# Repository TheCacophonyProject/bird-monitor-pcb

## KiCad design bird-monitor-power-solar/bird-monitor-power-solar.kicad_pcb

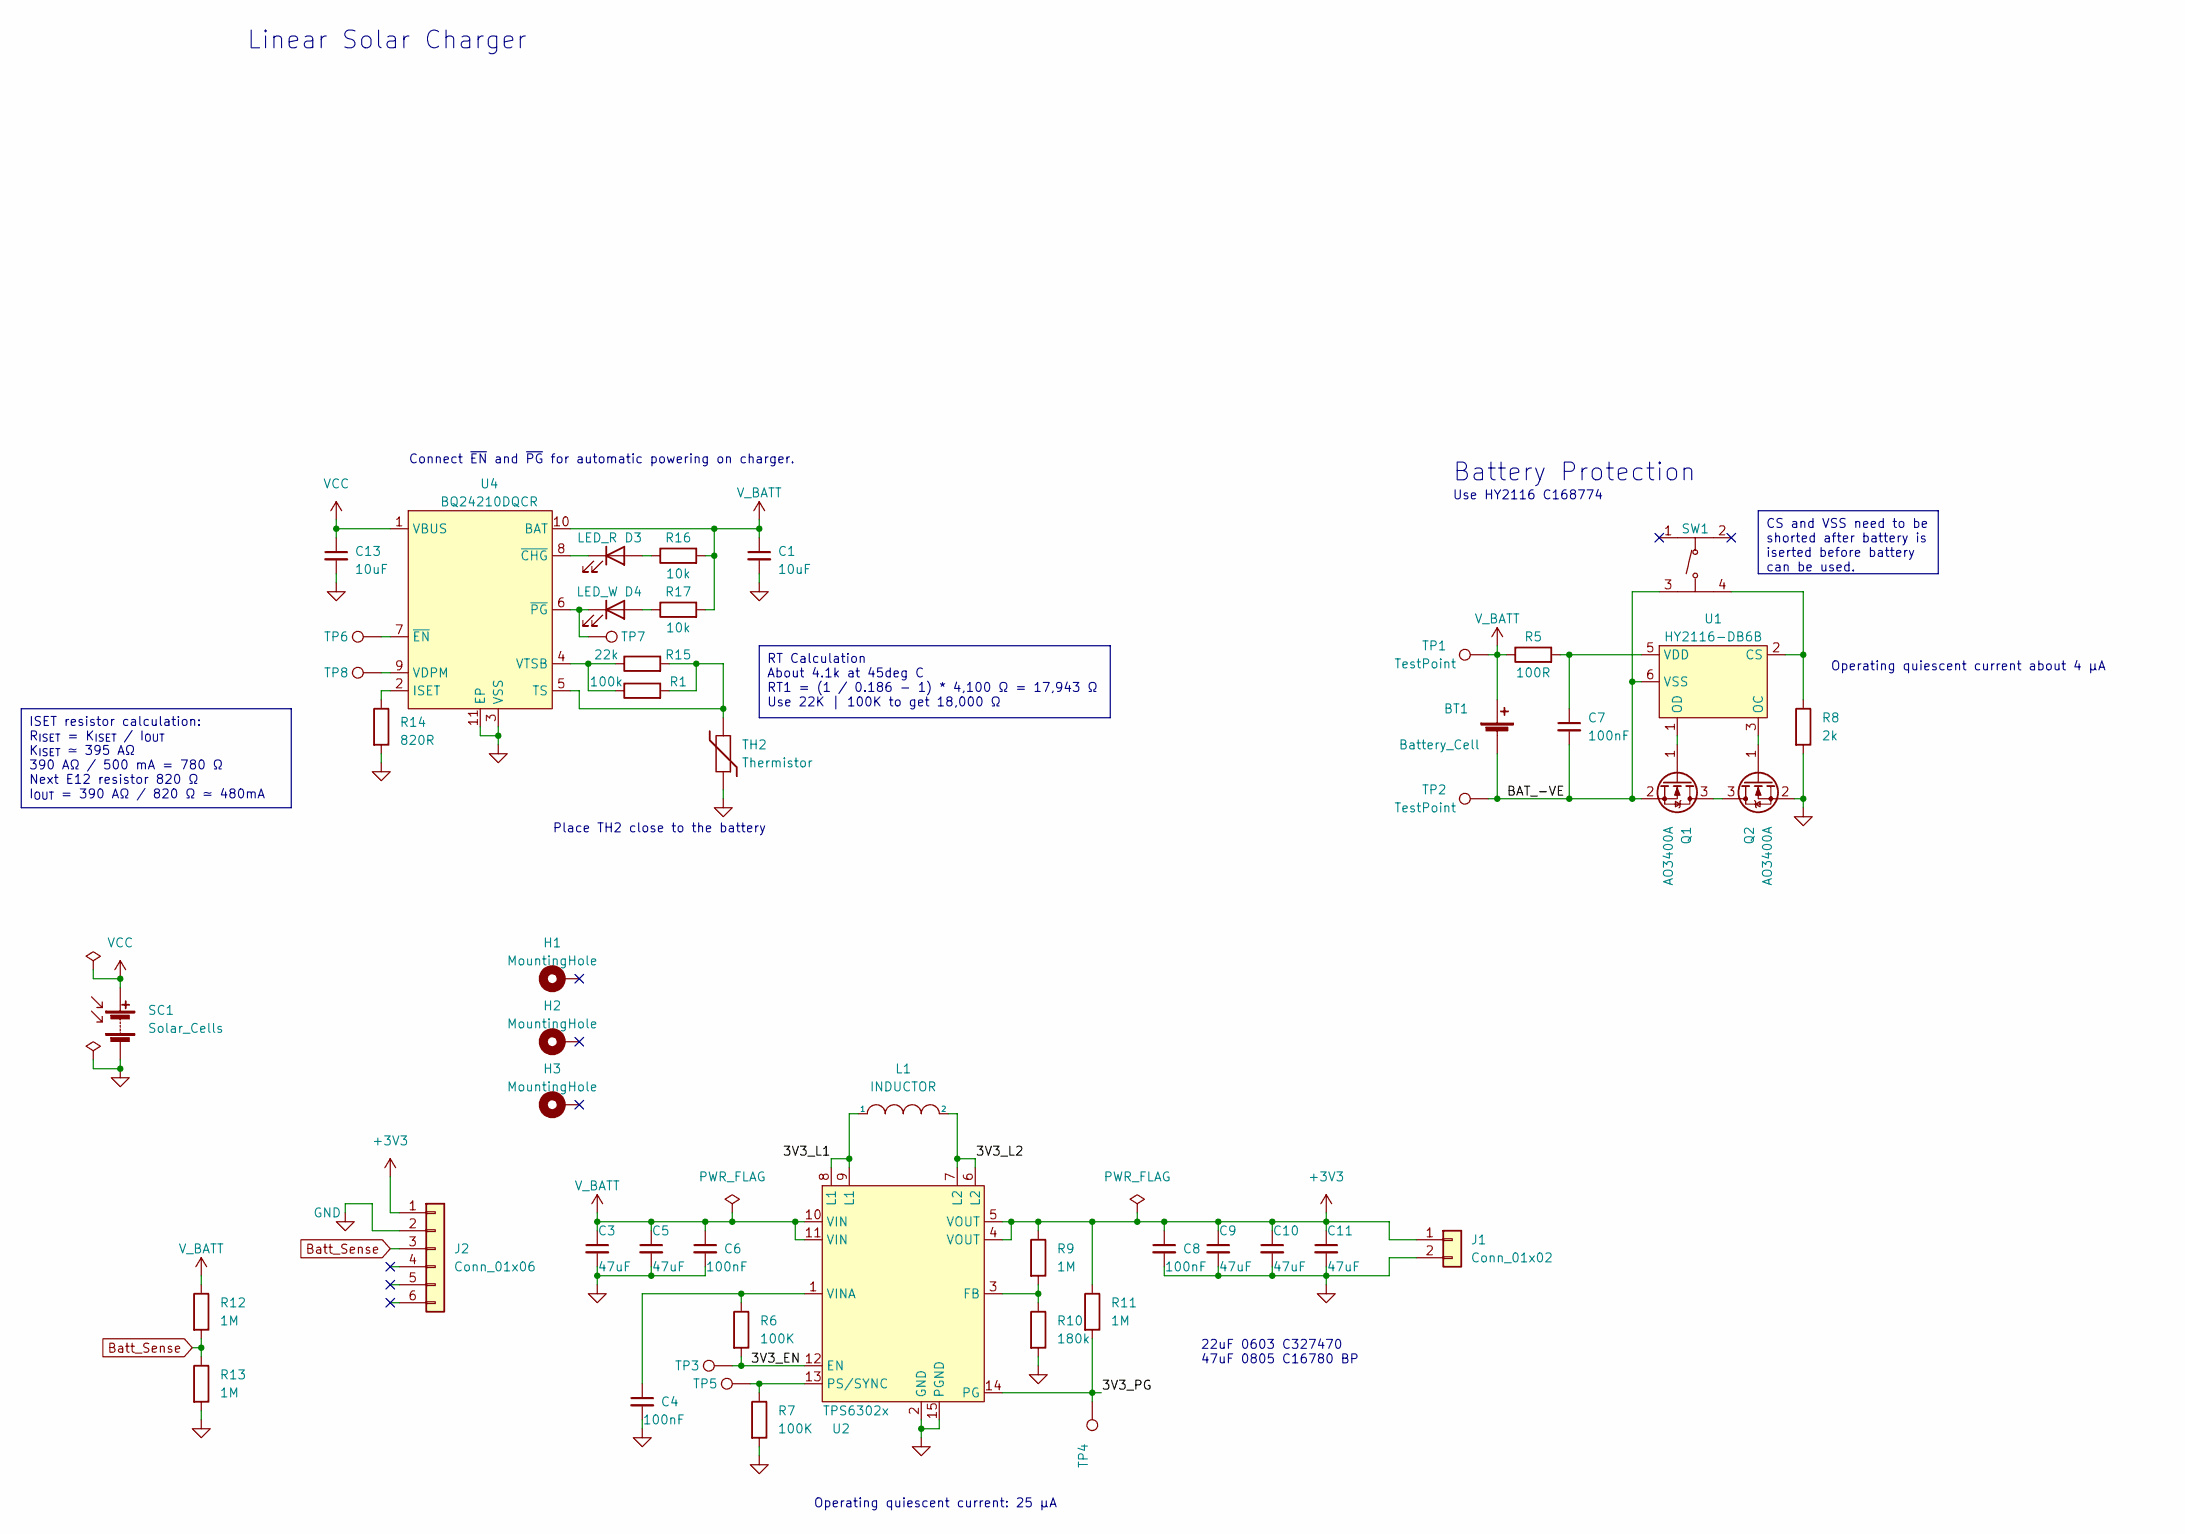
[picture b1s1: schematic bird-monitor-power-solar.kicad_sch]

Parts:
BT1: Battery_Cell; 18650_holder; LCSC C5290176
C1, C13: 10uF; C_0603_1608Metric; LCSC C96446
C3, C5, C9, C10, C11: 47uF; C_0805_2012Metric; LCSC C16780
C4, C6, C7, C8: 100nF; C_0402_1005Metric; LCSC C307331
D3: LED_R; LED_0603_1608Metric; LCSC C2286
D4: LED_W; LED_0603_1608Metric; LCSC C2290
H1, H2, H3: MountingHole; MountingHole_3.2mm_M3_DIN965_Pad
J1: Conn_01x02; PinHeader_1x02_P2.54mm_Vertical
J2: Conn_01x06; PinHeader_1x06_P2.54mm_Vertical
L1: INDUCTOR; IND-SMD_L6.6-W6.6_MCW-06XX; LCSC C169313
Q1, Q2: AO3400A; SOT-23; LCSC C20917
R1: 100k; R_0402_1005Metric; LCSC C25741
R5: 100R; R_0402_1005Metric; LCSC C25076
R6, R7: 100K; R_0402_1005Metric; LCSC C25741
R8: 2k; R_0603_1608Metric; LCSC C22975
R9, R11: 1M; R_0402_1005Metric; LCSC C26083
R10: 180k; R_0402_1005Metric; LCSC C409856
R12, R13: 1M; R_0603_1608Metric; LCSC C22935
R14: 820R; R_0603_1608Metric; LCSC C23253
R15: 22k; R_0402_1005Metric; LCSC C25768
R16, R17: 10k; R_0402_1005Metric; LCSC C25744
SC1: Solar_Cells; PinHeader_1x02_P2.54mm_Vertical
SW1: TS-1187A-B-A-B; SW-SMD_4P-L5.1-W5.1-P3.70-LS6.5-TL-2; LCSC Part C318884
TH2: Thermistor; R_0805_2012Metric; LCSC C95968
TP1, TP2, TP3, TP4, TP5, TP6, TP7, TP8: TestPoint; TestPoint_THTPad_D2.0mm_Drill1.0mm
U1: HY2116-DB6B; SOT-23-6; LCSC C168774
U2: TPS6302x; VSON-14_L4.0-W3.0-P0.50-BL-EP_TI_DSJ; LCSC C15483
U4: BQ24210DQCR; WSON-10-1EP_2x3mm_P0.5mm_EP0.84x2.4mm; LCSC Part C524795

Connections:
+3V3: C8.1, C9.1, C10.1, C11.1, J1.1, J2.1, R9.1, R11.1, U2.4 (VOUT), U2.5 (VOUT)
/3V3_EN: R6.2, TP3.1, U2.12 (EN)
/3V3_L1: L1.1, U2.8 (L1), U2.9 (L1)
/3V3_L2: L1.2, U2.6 (L2), U2.7 (L2)
/3V3_PG: R11.2, TP4.1, U2.14 (PG)
/BAT_-VE: BT1.2 (-), C7.2, Q1.2 (S), SW1.3, TP2.1, U1.6 (VSS)
Batt_Sense: J2.3, R12.2, R13.1
GND: C1.2, C3.2, C4.2, C5.2, C6.2, C8.2, C9.2, C10.2, C11.2, C13.2, J1.2, J2.2, Q2.2 (S), R7.2, R8.2, R10.2, R13.2, R14.2, SC1.2 (-), TH2.1, U2.2 (GND), U2.15 (PGND), U4.3 (VSS), U4.11 (EP)
unnamed: D3.2 (A), R16.1
unnamed: D3.1 (K), U4.8 (~CHG)
unnamed: D4.2 (A), R17.1
unnamed: D4.1 (K), TP7.1, U4.6 (~PG)
unnamed: Q1.3 (D), Q2.3 (D)
unnamed: Q1.1 (G), U1.1 (OD)
unnamed: Q2.1 (G), U1.3 (OC)
unnamed: R8.1, SW1.4, U1.2 (CS)
unnamed: C7.1, R5.2, U1.5 (VDD)
unnamed: R9.2, R10.1, U2.3 (FB)
unnamed: R7.1, TP5.1, U2.13 (PS/SYNC)
unnamed: C4.1, R6.1, U2.1 (VINA)
unnamed: R14.1, U4.2 (ISET)
unnamed: R1.2, R15.2, TH2.2, U4.5 (TS)
unnamed: TP8.1, U4.9 (VDPM)
unnamed: R1.1, R15.1, U4.4 (VTSB)
unnamed: TP6.1, U4.7 (~EN)
VCC: C13.1, SC1.1 (+), U4.1 (VBUS)
V_BATT: BT1.1 (+), C1.1, C3.1, C5.1, C6.1, R5.1, R12.1, R16.2, R17.2, TP1.1, U2.10 (VIN), U2.11 (VIN), U4.10 (BAT)

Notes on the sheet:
RT Calculation About 4.1k at 45deg C RT1 = (1 / 0.186 - 1) * 4,100 Ω = 17,943 Ω Use 22K | 100K to get 18,000 Ω
CS and VSS need to be shorted after battery is iserted before battery can be used.
ISET resistor calculation: R_{ISET} = K_{ISET} / I_{OUT} K_{ISET} ≃ 395 AΩ 390 AΩ / 500 mA = 780 Ω Next E12 resistor 820 Ω I_{OUT} = 390 AΩ / 820 Ω ≃ 480mA
Operating quiescent current about 4 μA
Battery Protection
Connect ~{EN} and ~{PG} for automatic powering on charger.
Use HY2116 C168774
Operating quiescent current: 25 μA
Place TH2 close to the battery
Linear Solar Charger
22uF 0603 C327470 47uF 0805 C16780 BP

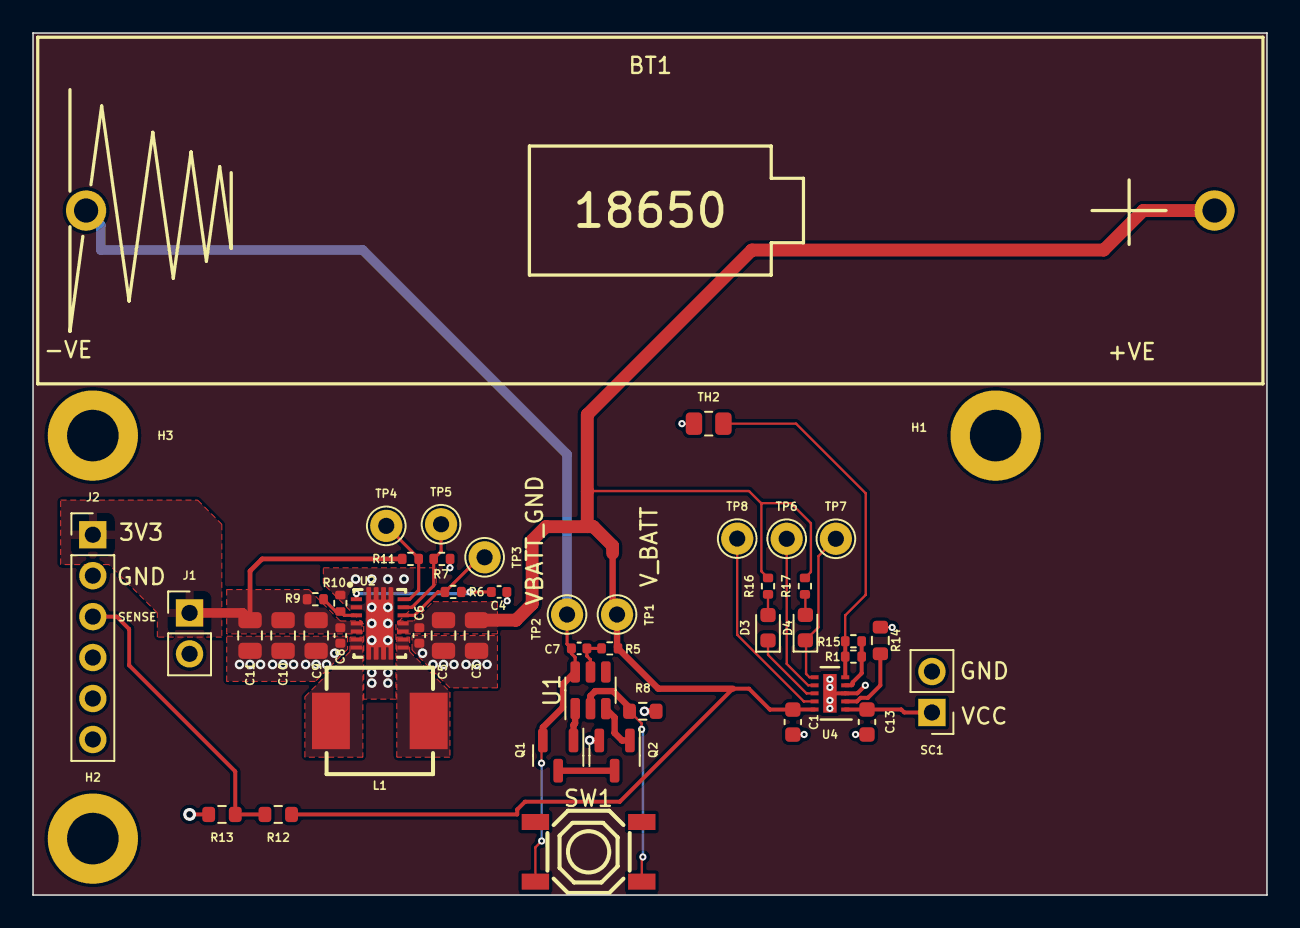
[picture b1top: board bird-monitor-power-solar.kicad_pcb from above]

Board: 4 copper layers, 76.5 x 53.5 mm, 50 parts (0 on the bottom side), 27 nets.

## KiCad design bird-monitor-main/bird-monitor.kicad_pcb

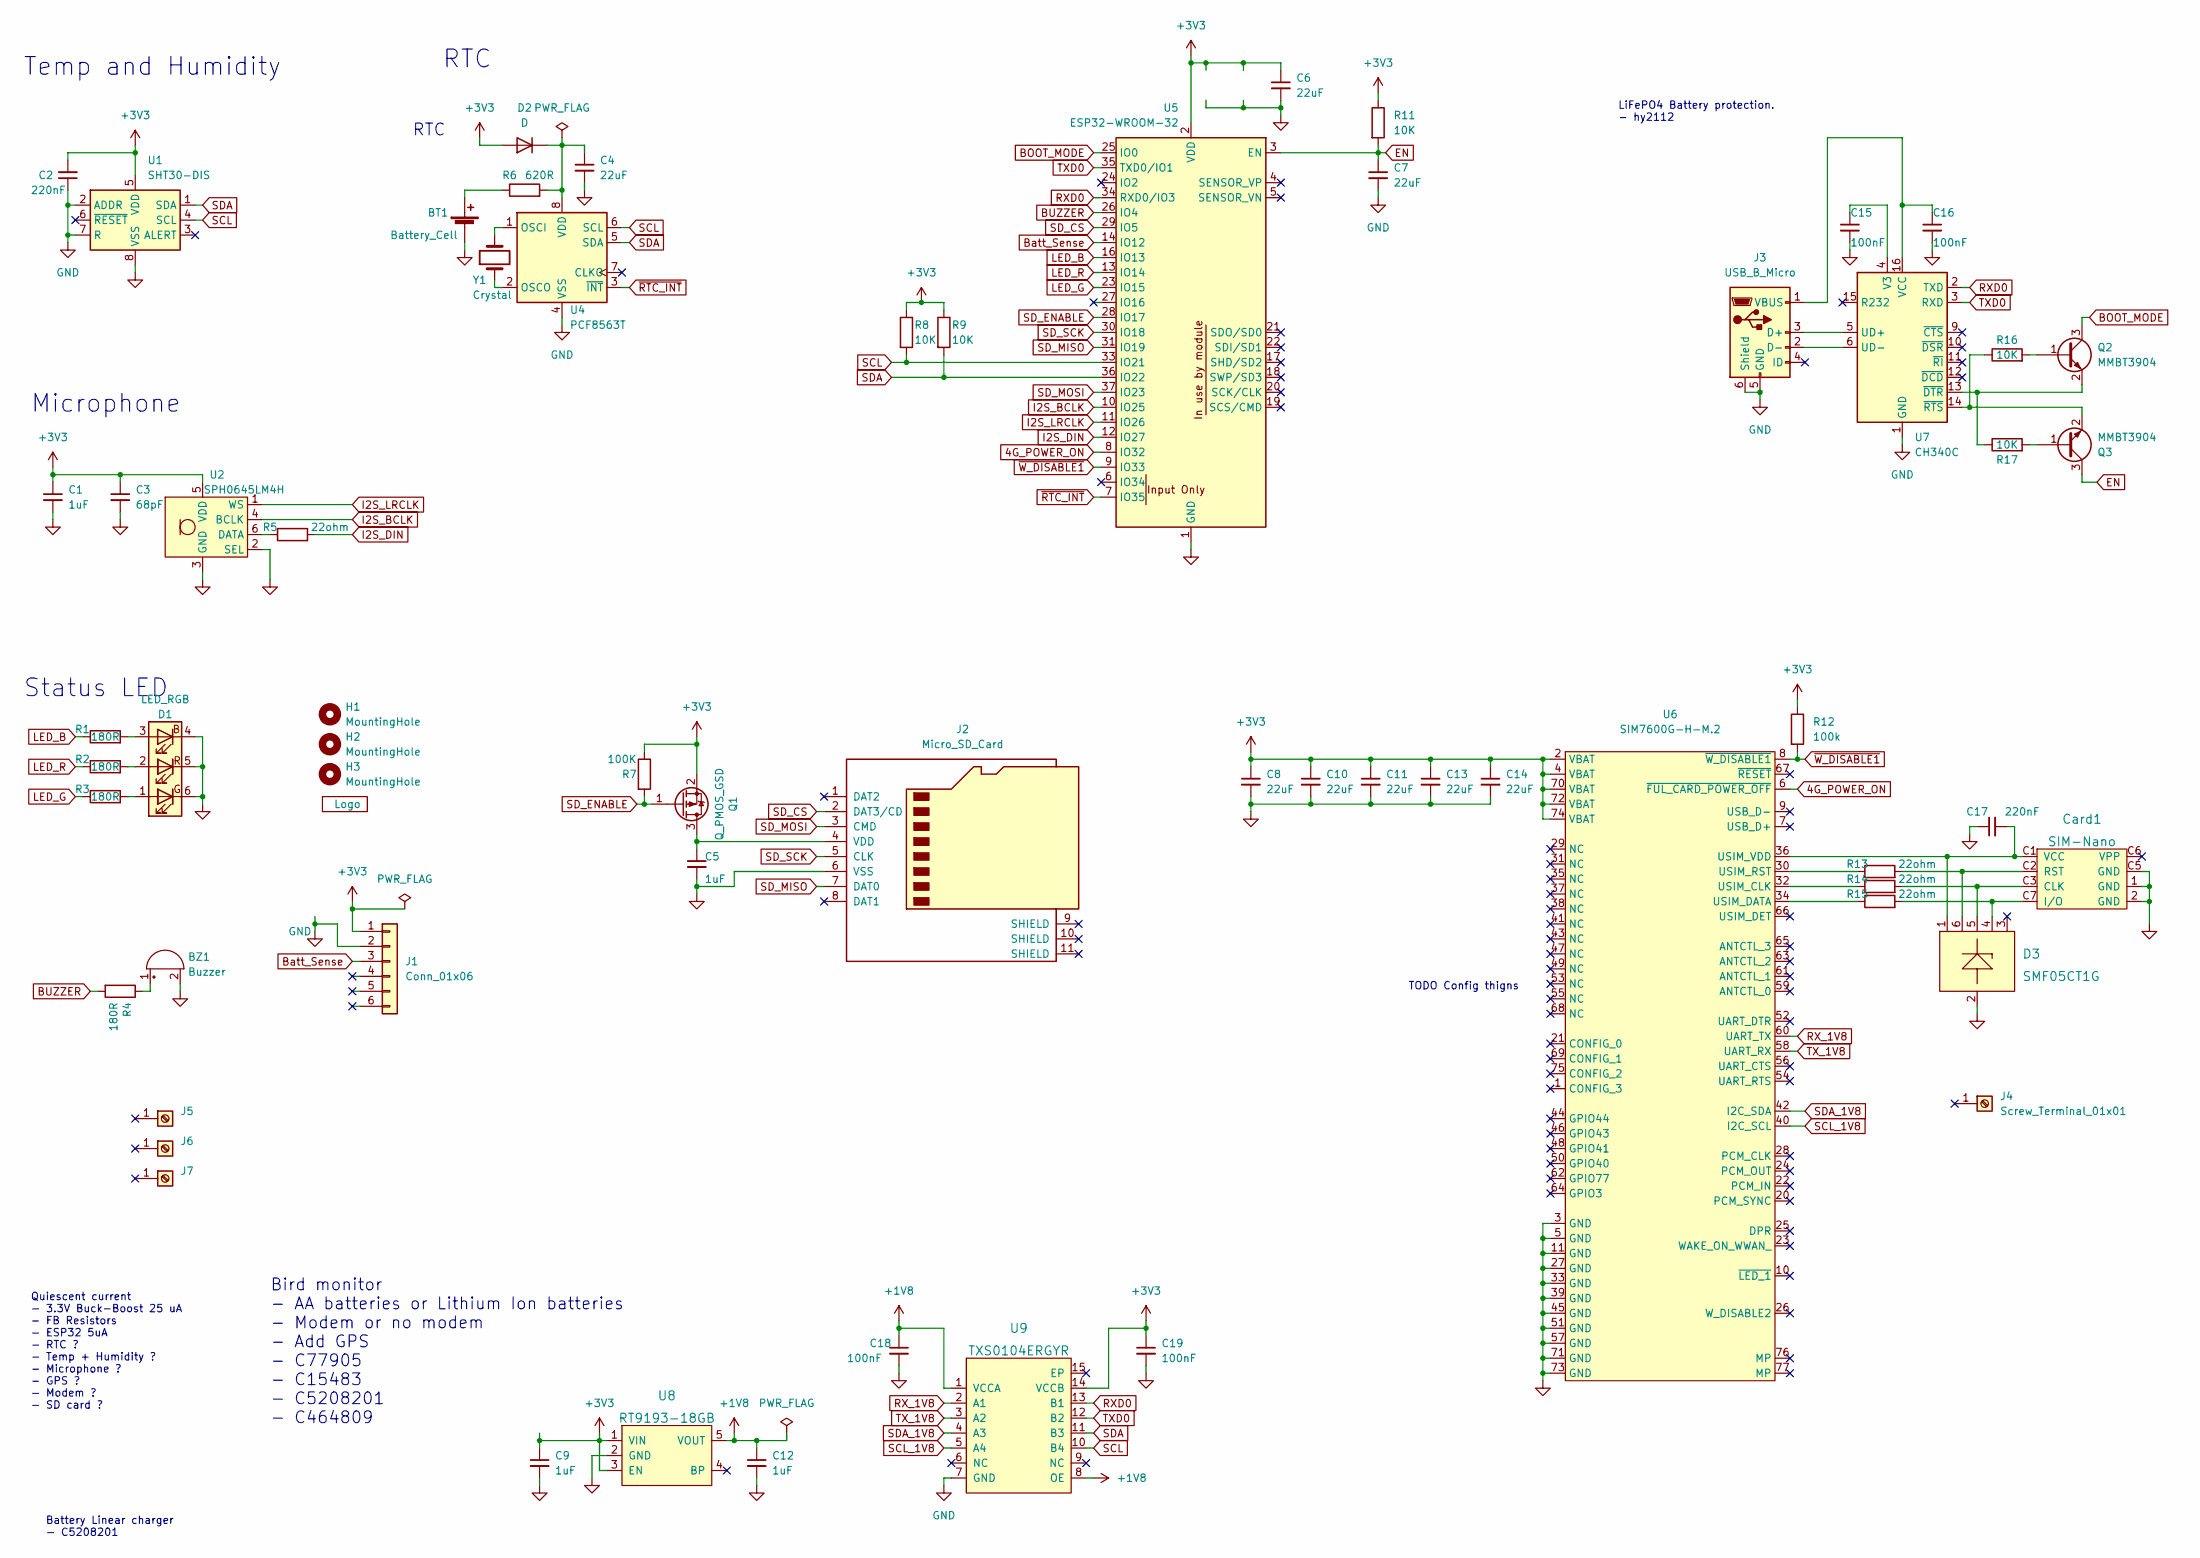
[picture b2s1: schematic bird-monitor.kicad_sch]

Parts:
BT1: Battery_Cell; CAP-SMD_FL11E
BZ1: Buzzer; BUZ-TH_BD9.0-P5.00-D0.6-FD; LCSC C96102
C1, C5, C9, C12: 1uF; C_0402_1005Metric; LCSC C52923
C2, C17: 220nF; C_0402_1005Metric; LCSC C16772
C3: 68pF; C_0402_1005Metric; LCSC C14441
C4, C6, C7, C8, C10, C11, C13, C14: 22uF; C_0603_1608Metric; LCSC C59461
C15, C16, C18, C19: 100nF; C_0402_1005Metric; LCSC C307331
Card1: SIM-Nano; LCSC C266889
D1: LED_RGB; LCSC C375568
D2: D; D_SOD-123F; LCSC C64898
D3: SMF05CT1G; SOT-363_L2.0-W1.3-P0.65-LS2.1-TL; LCSC C15879
H1, H2, H3: MountingHole; MountingHole_3.2mm_M3_DIN965_Pad
J1: Conn_01x06; PinHeader_1x06_P2.54mm_Vertical
J2: Micro_SD_Card; SD_Micro; LCSC C393941
J3: USB_B_Micro; 920-E52A2021S10100; LCSC C10418
J4: Screw_Terminal_01x01; SMD_M2_nut; LCSC C2928176
J5, J6, J7: Screw_Terminal_M2_L10; SMD_NUT_D5.6-HD3.6-L10.0; LCSC C2928171
Q1: Q_PMOS_GSD; SOT-23; LCSC C15127
Q2, Q3: MMBT3904; SOT-23; LCSC C20526
R1, R2, R3, R4: 180R; R_0603_1608Metric; LCSC C22828
R5, R13, R14, R15: 22ohm; R_0402_1005Metric; LCSC C25092
R6: 620R; R_0603_1608Metric; LCSC C23220
R7: 100K; R_0402_1005Metric; LCSC C25741
R8, R9, R11, R16, R17: 10K; R_0402_1005Metric; LCSC C25744
R12: 100k; R_0402_1005Metric; LCSC C25741
U1: SHT30-DIS; Sensirion_DFN-8-1EP_2.5x2.5mm_P0.5mm_EP1.1x1.7mm; LCSC C77361
U2: SPH0645LM4H; MIC_SPH0645LM4H-B; LCSC C2686054
U3: Logo; logo
U4: PCF8563T; SOIC-8_3.9x4.9mm_P1.27mm; LCSC C7440
U5: ESP32-WROOM-32; LCSC C701341
U6: SIM7600G-H-M.2; M.2; LCSC C2761526
U7: CH340C; SOIC-16_3.9x9.9mm_P1.27mm; LCSC C84681
U8: RT9193-18GB; SOT-23-5; LCSC C27416
U9: TXS0104ERGYR; VQFN-14_L3.5-W3.5-P0.50-BL-EP; LCSC Part C154926
Y1: Crystal; Crystal_SMD_3215-2Pin_3.2x1.5mm; LCSC C32346

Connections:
4G_POWER_ON: U5.8 (IO32), U6.6 (~FUL_CARD_POWER_OFF)
+1V8: C12.1, C18.1, U8.5 (VOUT), U9.1 (VCCA), U9.8 (OE)
+3V3: C1.1, C2.2, C3.1, C6.1, C8.1, C9.1, C10.1, C11.1, C13.1, C14.1, C19.1, D2.2 (A), J1.1, Q1.2 (S), R7.1, R8.1, R9.1, R11.1, R12.1, U1.5 (VDD), U2.5 (VDD), U5.2 (VDD), U6.2 (VBAT), U6.4 (VBAT), U6.70 (VBAT), U6.72 (VBAT), U6.74 (VBAT), U8.1 (VIN), U8.3 (EN), U9.14 (VCCB)
BOOT_MODE: Q2.3 (C), U5.25 (IO0)
BUZZER: R4.2, U5.26 (IO4)
Batt_Sense: J1.3, U5.14 (IO12)
EN: C7.1, Q3.3 (C), R11.2, U5.3 (EN)
GND: BT1.2 (-), BZ1.2 (+), C1.2, C2.1, C3.2, C4.2, C5.2, C6.2, C7.2, C8.2, C9.2, C10.2, C11.2, C12.2, C13.2, C14.2, C15.2, C16.2, C17.1, C18.2, C19.2, Card1.1 (GND), Card1.2 (GND), Card1.C5 (GND), D1.4 (BK), D1.5 (GK), D1.6 (RK), D3.2, J1.2, J2.6 (VSS), J3.5 (GND), J3.6 (Shield), U1.2 (ADDR), U1.7 (R), U1.8 (VSS), U1.9 (VSS), U2.2 (SEL), U2.3 (GND), U4.4 (VSS), U5.1 (GND), U5.15 (GND), U5.38 (GND), U5.39 (GND), U6.3 (GND), U6.5 (GND), U6.11 (GND), U6.27 (GND), U6.33 (GND), U6.39 (GND), U6.45 (GND), U6.51 (GND), U6.57 (GND), U6.71 (GND), U6.73 (GND), U7.1 (GND), U8.2 (GND), U9.7 (GND)
I2S_BCLK: U2.4 (BCLK), U5.10 (IO25)
I2S_DIN: R5.2, U5.12 (IO27)
I2S_LRCLK: U2.1 (WS), U5.11 (IO26)
LED_B: R1.1, U5.16 (IO13)
LED_G: R3.1, U5.23 (IO15)
LED_R: R2.1, U5.13 (IO14)
unnamed: BT1.1 (+), R6.1
unnamed: BZ1.1 (-), R4.1
unnamed: C4.1, D2.1 (K), R6.2, U4.8 (VDD)
unnamed: C5.1, J2.4 (VDD), Q1.3 (D)
unnamed: C15.1, U7.4 (V3)
unnamed: C16.1, J3.1 (VBUS), U7.16 (VCC)
unnamed: C17.2, Card1.C1 (VCC), D3.1, U6.36 (USIM_VDD)
unnamed: Card1.C2 (RST), D3.6, R13.2
unnamed: Card1.C3 (CLK), D3.5, R14.2
unnamed: Card1.C7 (I/O), D3.4, R15.2
unnamed: D1.1 (RA), R3.2
unnamed: D1.2 (GA), R2.2
unnamed: D1.3 (BA), R1.2
unnamed: J3.2 (D-), U7.6 (UD-)
unnamed: J3.3 (D+), U7.5 (UD+)
unnamed: Q2.1 (B), R16.2
unnamed: Q2.2 (E), R17.1, U7.13 (~DTR)
unnamed: Q3.1 (B), R17.2
unnamed: Q3.2 (E), R16.1, U7.14 (~RTS)
unnamed: R5.1, U2.6 (DATA)
unnamed: R13.1, U6.30 (USIM_RST)
unnamed: R14.1, U6.32 (USIM_CLK)
unnamed: R15.1, U6.34 (USIM_DATA)
unnamed: U4.1 (OSCI), Y1.2
unnamed: U4.2 (OSCO), Y1.1
RXD0: U5.34 (RXD0/IO3), U7.2 (TXD), U9.13 (B1)
RX_1V8: U6.60 (UART_TX), U9.2 (A1)
SCL: R8.2, U1.4 (SCL), U4.6 (SCL), U5.33 (IO21), U9.10 (B4)
SCL_1V8: U6.40 (I2C_SCL), U9.5 (A4)
SDA: R9.2, U1.1 (SDA), U4.5 (SDA), U5.36 (IO22), U9.11 (B3)
SDA_1V8: U6.42 (I2C_SDA), U9.4 (A3)
SD_CS: J2.2 (DAT3/CD), U5.29 (IO5)
SD_ENABLE: Q1.1 (G), R7.2, U5.28 (IO17)
SD_MISO: J2.7 (DAT0), U5.31 (IO19)
SD_MOSI: J2.3 (CMD), U5.37 (IO23)
SD_SCK: J2.5 (CLK), U5.30 (IO18)
TXD0: U5.35 (TXD0/IO1), U7.3 (RXD), U9.12 (B2)
TX_1V8: U6.58 (UART_RX), U9.3 (A2)
~RTC_INT: U4.3 (~INT), U5.7 (IO35)
~W_DISABLE1: R12.2, U5.9 (IO33), U6.8 (~W_DISABLE1)

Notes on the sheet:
Temp and Humidity
Battery Linear charger - C5208201
TODO Config thigns
RTC
Quiescent current - 3.3V Buck-Boost 25 uA - FB Resistors - ESP32 5uA - RTC ? - Temp + Humidity ? - Microphone ? - GPS ? - Modem ? - SD card ?
Status LED
Microphone
Bird monitor - AA batteries or Lithium Ion batteries - Modem or no modem - Add GPS - C77905 - C15483 - C5208201 - C464809
LiFePO4 Battery protection. - hy2112

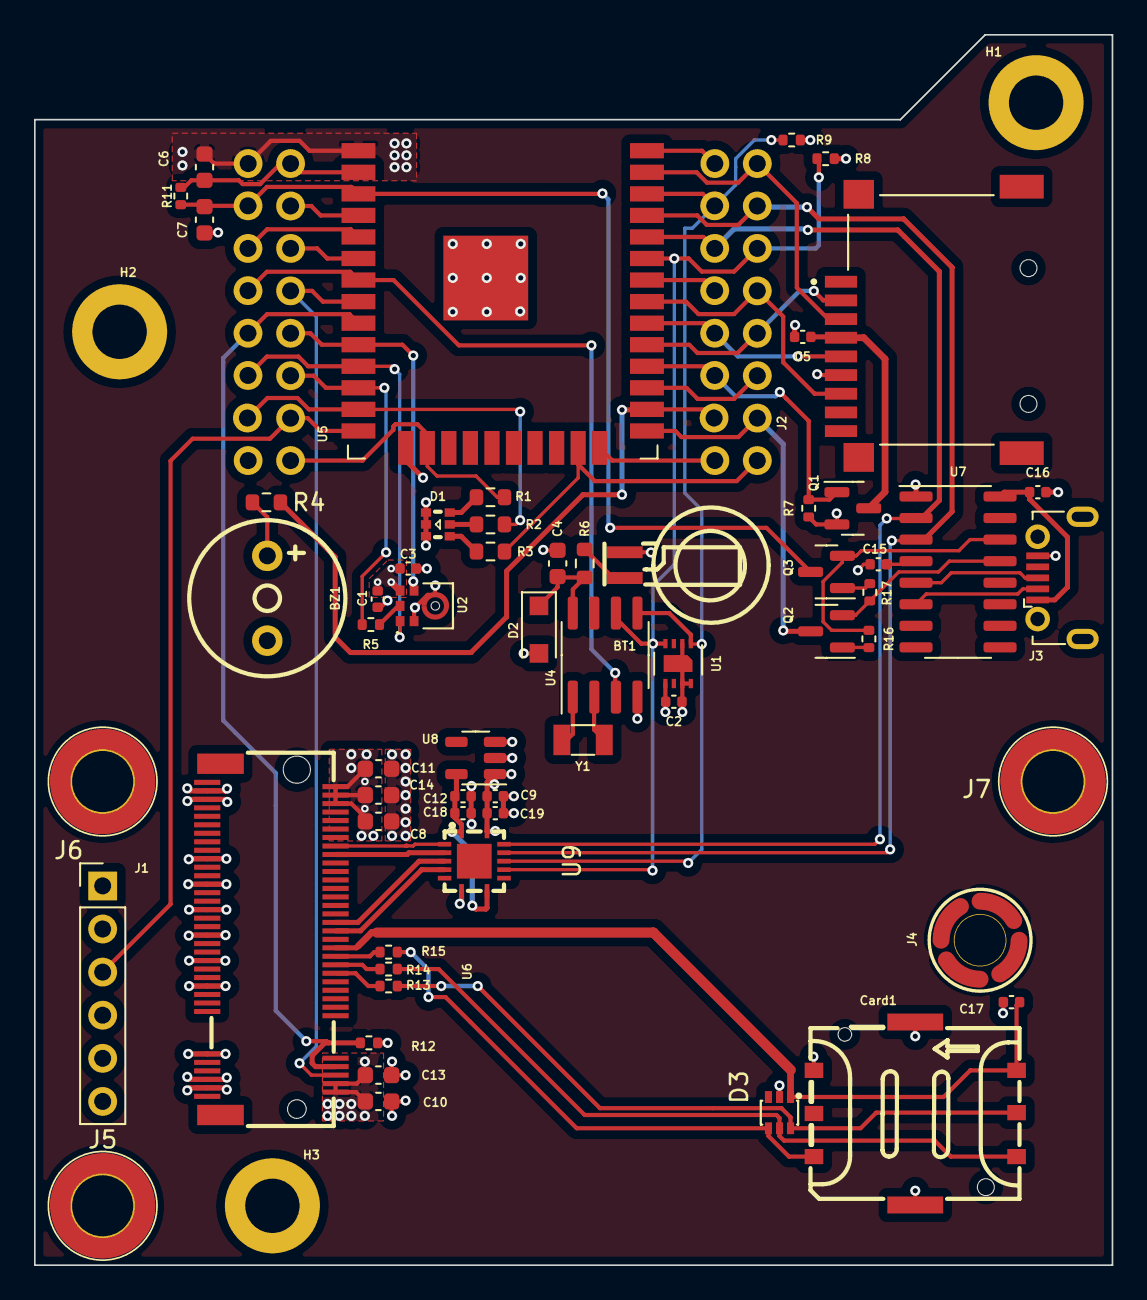
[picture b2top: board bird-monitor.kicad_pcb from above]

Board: 4 copper layers, 63.5 x 72.5 mm, 64 parts (1 on the bottom side), 54 nets.
